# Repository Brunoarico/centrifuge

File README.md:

# Centrífuga Seletora
Um projeto desenvolvido durante o ano de 2016, que foi desenvolvido em conjunto com alunos do Instituto de Farmácia, Arquitetura e Biologia da Universidade de São Paulo para o projeto do iGEM 2016 do grupo USP-UNIFESP, [Algaranha][igem2016].
O foco principal do projeto foi o de desenvolver uma centrífuga de pequeno porte a baixo custo, com as mesmas funcionalidades das microcentrífugas vendidas comercialmente por preços que superam a casa dos 3 mil reais.
Este projeto teve como base a construida pelo [BioHack Academy][biohackacademy]. 
Nosso primeiro protótipo teve ele como base onde adicionamos alguns melhoramentos como redução de fios, e a troca completa do software. 

Após encontrarmos diversos problemas na montagem inicial decidimos fazer uma versão completamente nova, com estrutura remodelada para reduzir a reverberação sonora, software completamente novo e mais modularizado e um hardware mais robusto mais a prova de falhas.
Ao final construimos uma microcentrífuga de uso geral em laboratório, construida utilizando um Arduíno Pró Mini e placas de MDF, em essência, que possui as seguintes especificações:

- Tensão de operação 110V/220V;
- Capacidade para 8 microtubos de 1.5mL;
- Rotação mínima 2000 RPM e máxima de 15000 RPM;
- Função spin rápido;
- Função ajuste de tempo de operação, taxa de aceleração e velocidade de operação;
- Verificação de segurança por software;

Site: linux.ime.usp.br/~brunobra
Email: brunoarico@gmail.com

[biohackacademy]: <http://biohackacademy.github.io/biofactory/class/5-centrifuge/>
[igem2016]: <http://2016.igem.org/Team:USP_UNIFESP-Brazil>

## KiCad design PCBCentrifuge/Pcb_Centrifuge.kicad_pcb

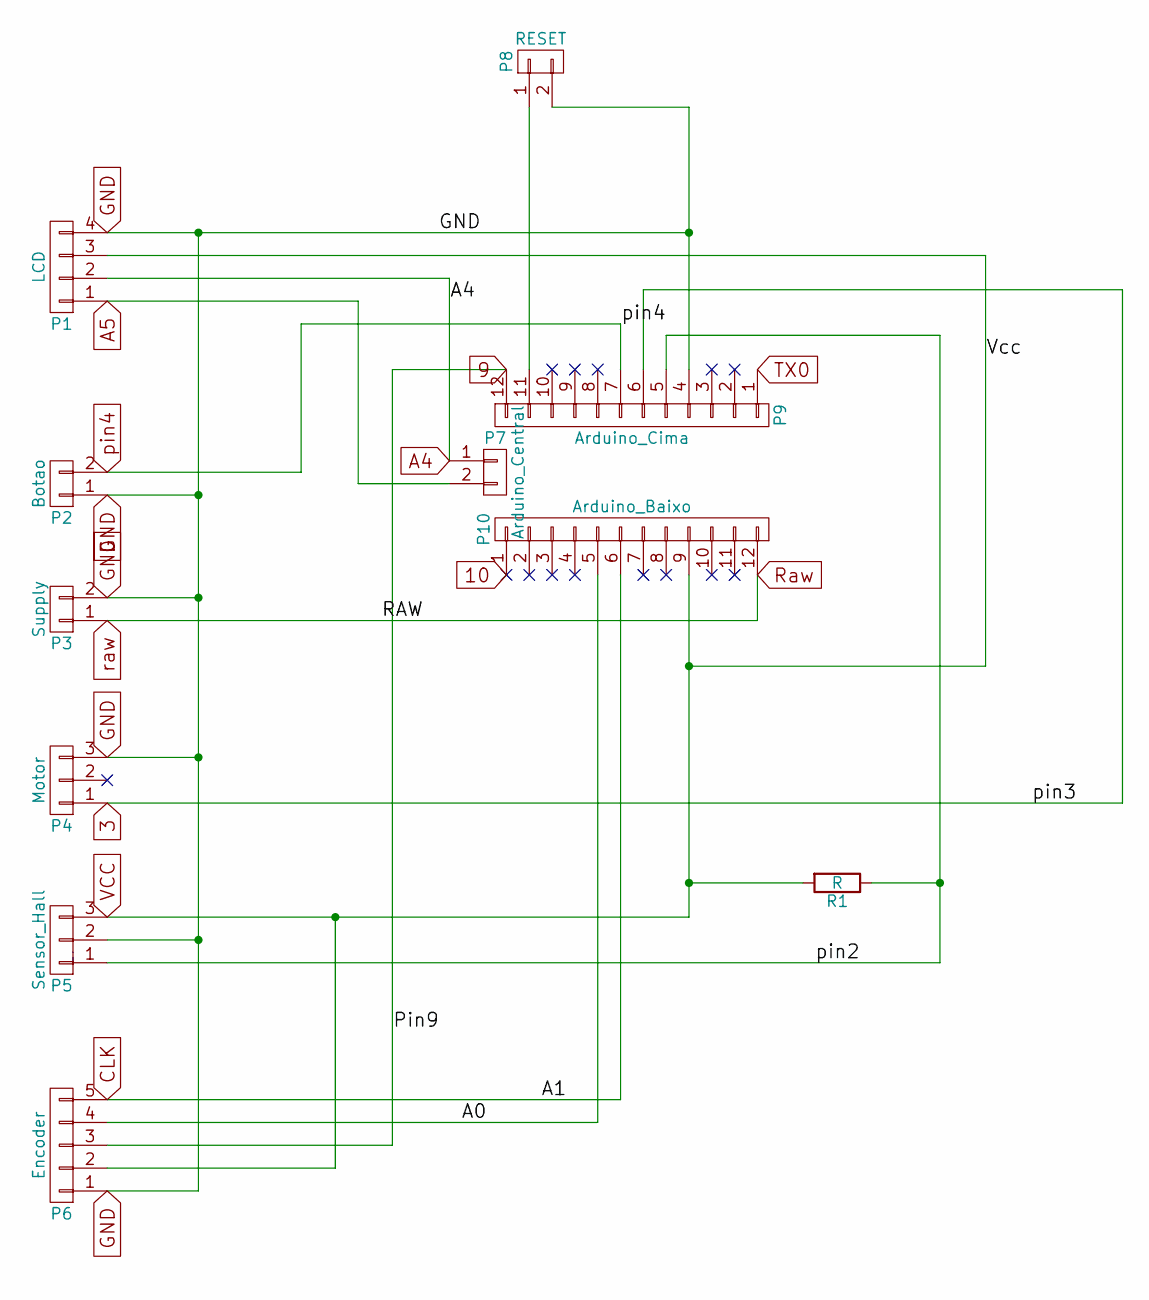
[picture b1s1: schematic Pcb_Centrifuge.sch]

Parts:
P1: LCD; Pin_Header_Straight_1x04
P2: Botao; Pin_Header_Straight_1x02
P3: Supply; Pin_Header_Straight_1x02
P4: Motor; Pin_Header_Straight_1x03
P5: Sensor_Hall; Pin_Header_Straight_1x03
P6: Encoder; Pin_Header_Straight_1x05
P7: Arduino_Central; Pin_Header_Straight_1x02
P8: RESET; Pin_Header_Straight_1x02
P9: Arduino_Cima; Socket_Strip_Straight_1x12
P10: Arduino_Baixo; Socket_Strip_Straight_1x12
R1: R; Resistor_Horizontal_RM15mm

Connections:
3: P4.1, P9.6
9: P6.3, P9.12
10: P10.1
/A0: P6.4, P10.5
/pin2: P5.1, P9.5, R1.1
A4: P1.2, P7.1
A5: P1.1, P7.2
CLK: P6.5, P10.6
GND: P1.4, P2.1, P3.2, P4.3, P5.2, P6.1, P8.2, P9.4
unnamed: P8.1, P9.11
Raw: P3.1, P10.12
TX0: P9.1
VCC: P1.3, P5.3, P6.2, P10.9, R1.2
pin4: P2.2, P9.7

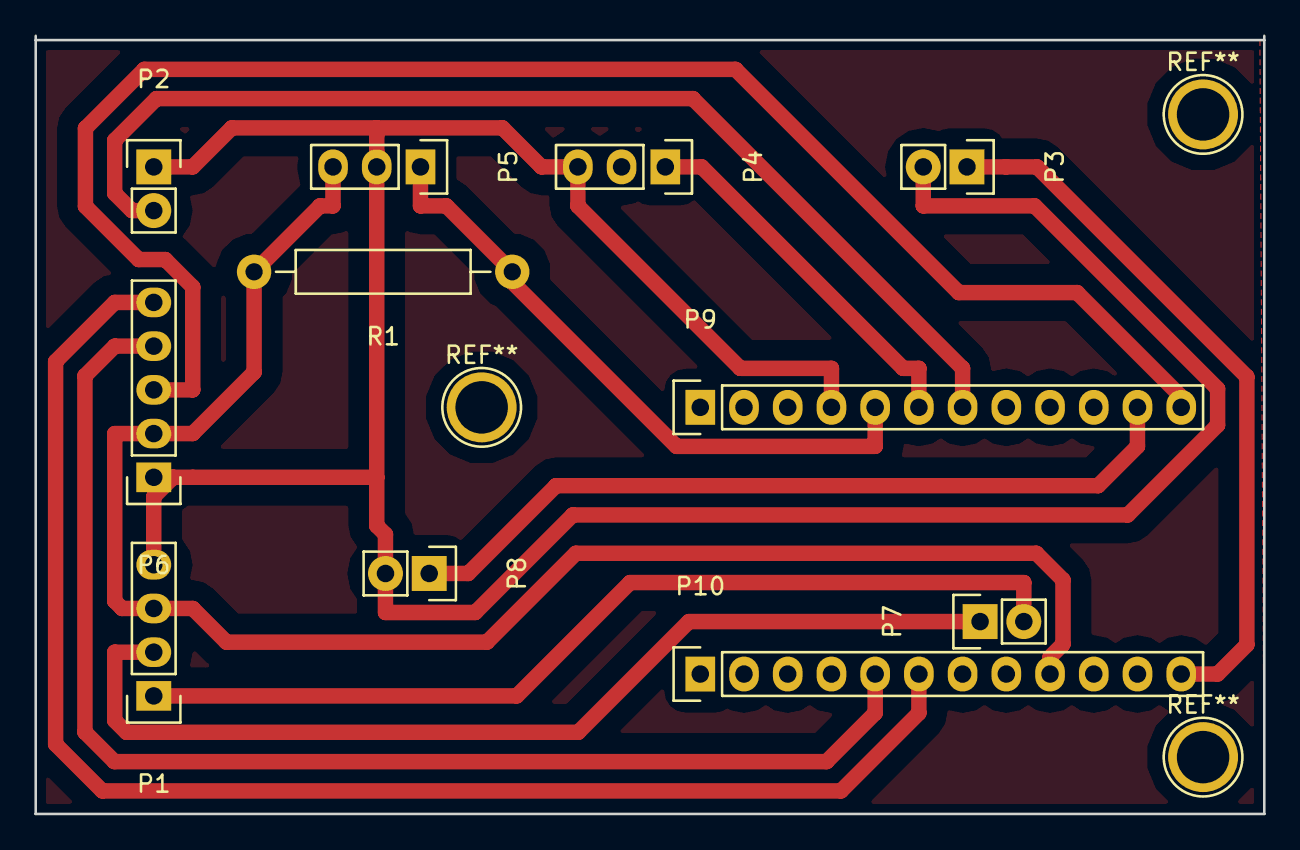
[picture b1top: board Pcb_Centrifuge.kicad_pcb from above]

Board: 2 copper layers, 71.4 x 45.2 mm, 11 parts (0 on the bottom side), 12 nets.

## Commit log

2018-01-04 add some files
